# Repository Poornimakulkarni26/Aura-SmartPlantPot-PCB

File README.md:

# Aura Smart Plant Pot 🌱

## Overview

It is a smart plant-care hardware platform designed to simplify plant maintenance through real-time visual feedback.

The PCB interfaces with a soil moisture sensor and uses a programmable RGB LED to indicate soil conditions through color codes. Powered by a battery and controlled by a Seeed Studio XIAO SAMD21, Aura is optimized for low-power operation and can be embedded into decorative plant pots, desktop planters, indoor gardens, or educational plant-monitoring systems.

Instead of requiring a mobile app or display, Aura communicates plant health using instantly recognizable colors, making plant care accessible and intuitive.

## Board Preview

## Features

✅ Soil Moisture Monitoring

✅ RGB Color-Based Status Indication

✅ Battery Powered Operation

✅ Power ON/OFF Switch

✅ Compact PCB Form Factor

✅ External Soil Moisture Sensor Interface

✅ Low Power Embedded Design

✅ USB-C Programming via XIAO SAMD21

## Color Indication Scheme

Aura uses color feedback to communicate the condition of the plant.

Color	Condition🔴 Red	Soil Extremely Dry
🟠 Amber	Water Required Soon
🟡 Yellow	Low Moisture Level
🟢 Green	Optimal Moisture
🔵 Blue	High Moisture
🟣 Purple	Sensor/Error/Future Status Extension

Threshold values can be customized in firmware according to plant type and soil characteristics.
The compact layout was designed to fit within smart planter enclosures while maintaining accessibility to programming and sensor connections.

## Applications
Indoor Plant Monitoring
Smart Flower Pots
Office Desk Plants
Educational IoT Projects
Sustainable Agriculture Demonstrations
Low-Power Sensor Platforms
Temperature Monitoring
Humidity Monitoring
Rechargeable Battery Management

---
 
## Getting Started
 
### View the Design
1. Install [KiCad](https://www.kicad.org/) (v7+ recommended)
2. Clone this repo:
```bash
   git clone https://github.com/Poornimakulkarni26/pocket-arcade.git
```
3. Open the `.kicad_pro` file in KiCad

---

## Author
 
**Poornima Kulkarni**
Embedded Systems & Industrial Automation Engineer
 
- GitHub: [@Poornimakulkarni26](https://github.com/Poornimakulkarni26)

---
## License
 
This project is open-source under the [MIT License](LICENSE).

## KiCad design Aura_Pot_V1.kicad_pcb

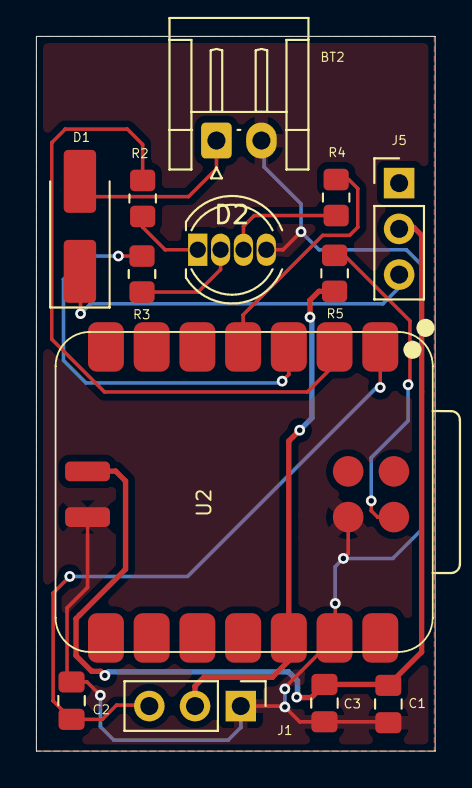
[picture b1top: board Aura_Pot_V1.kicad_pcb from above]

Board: 2 copper layers, 22.2 x 39.7 mm, 13 parts (0 on the bottom side), 13 nets.

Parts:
BT2: Battery; JST_EH_S2B-EH_1x02_P2.50mm_Horizontal
C1: 0.1uF; C_0805_2012Metric_Pad1.18x1.45mm_HandSolder
C2: 100nF; C_0805_2012Metric_Pad1.18x1.45mm_HandSolder
C3: 10uF; C_0805_2012Metric_Pad1.18x1.45mm_HandSolder
D1: D_Shockley; D_SMA_Handsoldering
D2: LED_RGBK; LED_D5.0mm-4_RGB
J1: Conn_01x03_Pin; PinHeader_1x03_P2.54mm_Vertical
J5: Switch; PinHeader_1x03_P2.54mm_Vertical
R2, R3, R4: 220; R_0805_2012Metric_Pad1.20x1.40mm_HandSolder
R5: 10k; R_0805_2012Metric_Pad1.20x1.40mm_HandSolder
U2: XIAO-SAMD21-SMD

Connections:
/3V3_SENSOR: J1.2, R5.2, U2.12 (3V3)
/SOIL_SIGNAL: C2.1, J1.3, U2.1 (PA02_A0_D0)
GND: BT2.2 (-), C1.2, C2.2, C3.2, D2.4 (K), J1.1, U2.13 (GND), U2.16 (GND), U2.20 (GND)
unnamed: BT2.1 (+), D1.2 (A)
unnamed: D1.1 (K), J5.3
unnamed: D2.3 (BA), R4.1
unnamed: D2.2 (GA), R3.1
unnamed: D2.1 (RA), R2.1
unnamed: R2.2, U2.2 (PA4_A1_D1)
unnamed: R3.2, U2.3 (PA10_A2_D2)
unnamed: R4.2, U2.4 (PA11_A3_D3)
SWCLK: R5.1, U2.18 (PA30_SWCLK)
Vin: C1.1, C3.1, J5.2, U2.15 (VIN)
